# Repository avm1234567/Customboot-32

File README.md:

<h1 align="center">🚀 CustomBoot-32</h1>

<h2 align="center">✨ SRA Eklavya 2025</h2>

## 📑 Table of Contents
* [About the Project](#-about-the-project)  
  - [Aim](#aim)  
  - [Description](#description)  
  - [Tech-Stack](#tech-stack)  
  - [File Structure](#file-structure)  
* [Getting Started](#getting-started)  
  * [Installation](#installation)  
* [Usage](#usage)  
* [Results and Demo](#results-and-demo)  
* [Future Work](#future-work)  
* [Report](#report)
* [Troubleshooting](#troubleshooting)  
* [Contributors](#contributors)  
* [Mentors](#mentors)  
* [Resources](#resources)  
* [Acknowledgements](#acknowledgements)  

---

# ⭐ About the Project

## Aim
Designing a custom PCB with OTA support and a dual-image Bootloader using ESP32 WROOM-32E and STM32F103C8T6.

## Description
The project focuses on creating a custom PCB that integrates the Blue Pill (STM32F103C8T6) with ESP32 WROOM-32E.  
The ESP32 hosts a website, receives two firmwares via OTA, creates memory partitions, and initializes a File System in one of the partitions.  

On the STM side, a dual-image Bootloader requests firmware based on user input, verifies it, allocates it in flash memory, and executes it.  
The firmware transfer is carried out via **UART**.

## Tech-Stack
### Coding Language
<div style="display:flex; align-items:center; margin-bottom:8px;">
  
  <span style="background:#ff6f3c; color:white; padding:4px 10px; border-radius:4px; font-weight:bold;">
    Embedded C
  </span>
</div>

### Libraries
<div style="display:flex; align-items:center; margin-bottom:8px;">
  
  <span style="background:#ff6f3c; color:white; padding:4px 10px; border-radius:4px; font-weight:bold;">
    HAL
  </span>
</div>

<div style="display:flex; align-items:center; margin-bottom:8px;">
  
  <span style="background:#ff6f3c; color:white; padding:4px 10px; border-radius:4px; font-weight:bold;">
    LibOpenCM3
  </span>
</div>

### File Protocol
<div style="display:flex; align-items:center; margin-bottom:8px;">
  
  <span style="background:#ff6f3c; color:white; padding:4px 10px; border-radius:4px; font-weight:bold;">
    SPIFFS
  </span>
</div>

### Communication Protocols
<div style="display:flex; align-items:center; margin-bottom:8px;">
  
  <span style="background:#ff6f3c; color:white; padding:4px 10px; border-radius:4px; font-weight:bold;">
    UART
  </span>
</div>
<div style="display:flex; align-items:center; margin-bottom:8px;">
  
  <span style="background:#ff6f3c; color:white; padding:4px 10px; border-radius:4px; font-weight:bold;">
    OTA
  </span>
</div>
<br><br>

<br><br>

## 📁 File Structure

```
.
├── assets  #All images and test videos
│   ├── 2WayUART.mp4
│   ├── 3D-view back.png
│   ├── 3D-view.png
│   ├── EmbedC.png
│   ├── Final_PCB.png
│   ├── HAL.png
│   ├── LibOpenCM3.png
│   ├── OTA.png
│   ├── PCBSC1.png
│   ├── PCBSC2.png
│   ├── Routing.png
│   ├── SimpleBootloader.mp4
│   ├── SPIFFS.png
│   ├── UART.png
│   ├── website.png
│   ├── Wireless_CMD_Test.mp4
│   └── WorkingVideo.mp4
├── CustomBoot-32  #All the firmwares for both ESP as well as STM
│   ├── 1. OTA
│   ├── 2. Dual_Image_Bootloader
│   ├── 3. ESP_STM_UART1
│   ├── 4. ESP_STM_UART2
│   ├── 5. ESP_TO_STM_FIRMWARE_VIA_UART
│   ├── 6. ESP_STM_FILE_CRC
│   ├── 7. Controling_ESP_GPIO_Wirelessly
│   └── 8. Wireless_Firmware_Selection_ESP_STM(Additional)
├── Documentation  #Detailed documentation of the project
│   └── Final_DOC.pdf
├── Gerber files  #Files made for fabrication of PCB
│   ├── 4 SRA-B_Cu.gbr
│   ├── 4 SRA-B_Mask.gbr
│   ├── 4 SRA-B_Paste.gbr
│   ├── 4 SRA-B_Silkscreen.gbr
│   ├── 4 SRA-drlnew.zip
│   ├── 4 SRA-drl.rpt
│   ├── 4 SRA-Edge_Cuts.gbr
│   ├── 4 SRA-F_Cu.gbr
│   ├── 4 SRA-F_Mask.gbr
│   ├── 4 SRA-F_Paste.gbr
│   ├── 4 SRA-F_Silkscreen.gbr
│   ├── 4 SRA-job.gbrjob
│   ├── 4 SRA-NPTH-drl.gbr
│   ├── 4 SRA-NPTH-drl_map.gbr
│   ├── 4 SRA-PTH-drl.gbr
│   └── 4 SRA-PTH-drl_map.gbr
├── README.md
└── Schematic files  #Schematics of our PCB
    ├── 4 SRA.kicad_pcb
    ├── 4 SRA.kicad_sch
    └── untitled.kicad_sch

```

---

## 🚀 Getting Started

### Installation
1. Clone the repo  
   ```bash
   git clone https://github.com/avm1234567/Customboot-32.git
   ```
2. Navigate to the project directory  
   ```bash
   cd CustomBoot-32
   ```

---

## Usage

The codes used in our project are in the 'CustomBoot-32' directory. 

### 1. OTA

- From the CustomBoot-32 directory head to the OTA directory.
```
cd 1. OTA
```

- In the code enter the SSID and password of your wifi in line 16 and 17.
```
#define WIFI_SSID "Your_SSID"
#define WIFI_PASS "Your_Password"
```

- Then open ESP-IDF Powershell and build the project.
```
idf.py fullclean
idf.py build
```

- After the build is complete flash it.
```
idf.py flash monitor 
```

### 2. Dual_Image_Bootloader

- To generate the bin files open this project in STM32CubeIDE and build it 

- To flash this Code use STM32CubeProgrammer. Change your directory to Dual image bootloader directory. 

- After opening the directory first flash the LED_BLINK_2 bin file into STM-32 at the Start Address '0x08006000'. The path for the bin is: 
```
CustomBoot-32/2. Dual_Image_Bootloader/LED_BLINK_2/Debug/LED_BLINK_2.bin
```

- After flashing the first bin file flash the LED_BLINK bin file into STM-32 at the Start Address '0x08004000'. The path for the bin is:
```
CustomBoot-32/2. Dual_Image_Bootloader/LED_BLINK/Debug/LED_BLINK.bin
```

- Lastly, flash the Bootloader at the Start Address '0x08000000'. The path for the bin is:
```
CustomBoot-32/2. Dual_Image_Bootloader/Learning_Bootloader/Debug/Learning_Bootloader.bin
```

- Press the 'Start Programming' button to run the program.

### 3. ESP_STM_UART1

- To run the ESP side of the code change your directory to 'ESP_STM_COMM'.
```
cd 3. ESP_STM_UART1\ESP_STM_COMM
```

- After that build the code and flash it 
```
idf.py fullclean
idf.py build
idf.py flash monitor 
```

- To flash the STM code, open STM32CubeIDE and generate the build files.

- After generating flash the bin file into the STM using STM32CubeProgrammer at Start Address '0x08000000'

### 4. ESP_STM_UART2

- To run the ESP side of the code change your directory to 'ESP_STM_COMM'.
```
cd 3. ESP_STM_UART2\ESP_STM_COMM
```

- After that build the code and flash it 
```
idf.py fullclean
idf.py build
idf.py flash monitor 
```

- To flash the STM code, open STM32CubeIDE and generate the build files.

- After generating flash the bin file into the STM using STM32CubeProgrammer at Start Address '0x08000000'.

### 5. ESP_TO_STM_FIRMWARE_VIA_UART

-- To run the ESP side of the code change your directory to 'OTA'.
```
cd 5. ESP_TO_STM_FIRMWARE_VIA_UART\OTA
```

- After that build the code and flash it 
```
idf.py build
idf.py flash monitor 
```

- To flash the STM code, open STM32CubeIDE and generate the build files. You will find the bin files in the path
```
CustomBoot-32/5. ESP_TO_STM_FIRMWARE_VIA_UART/Learning_Bootloader/Debug/Learning_Bootloader.bin
```

- After generating flash the bin file into the STM using STM32CubeProgrammer at Start Address '0x08000000'.

### 6. ESP_STM_FILE CRC

- Download libopencm3 by cloning it to run bootloader file
```
git clone https://github.com/libopencm3/libopencm3.git
cd libopencm3
```
- After that flash the ESP32 in the directory
```
idf.py fullclean
CustomBoot-32/6. ESP_STM_FILE_CRC/OTA
idf.py build flash monitor
```

### 7. Controling_ESP_GPIO_Wirelessly
- Firstly fullclean, then build and flash the project.
```
idf.py fullclean
idf.py build
idf.py flash monitor
```

### 8. Wireless_Firmware_Selection
- Download libopencm3 by cloning it to run bootloader file
```
git clone https://github.com/libopencm3/libopencm3.git
cd libopencm3
```
- After that flash the ESP32 in the directory
```
idf.py fullclean
CustomBoot-32/8. Wireless_Firmware_Selection_ESP_STM(Additional)/OTA
idf.py build flash monitor
```

## 📸 Results

**Screenshot of our custom PCB:**  

|            Front            |            Back            |
| --------------------------- | -------------------------- |
|  |  |

## Demo:  
[Working Demo of final PCB](https://drive.google.com/file/d/1Z0VfDI0KjEA28zM6vQ-hMSaG2jekwzWR/view?usp=drive_link)  

For other results and test videos, please check our [Google Drive](https://drive.google.com/drive/folders/1JogM4m4yME66ZIJGMlyX8mcmxp7ndMSk?usp=drive_link).

## Report
Refer our own [report](https://drive.google.com/file/d/13CS2zIfVXfLGR-wP4OjCv9lpuOwN3wu8/view?usp=drive_link) of project where we explain the entire process in detail.

## 🛠 Troubleshooting
* ERC rule check errors in PCB schematics.  
* Routing issues in compact areas while adhering to manufacturer constraints.  
* Wi-Fi SSID and password options not appearing in Menuconfig.  
* CMakeLists errors affecting SPIFFS initialization.  
* Partition table not being detected.  
* SPIFFS initialization failure at runtime.  
* Favicon loading errors.  
* OTA binaries containing unnecessary bloatware.  
* UART initialization issues.  
* Binary file transfer failures.  
* Errors in custom file protocol implementation.  
* End-byte transmission errors during communication.  
* Application jump not functioning correctly (MSP not set).  
* Correct HAL-like application jump with LibOpenCM3.  
* Schematic issues resolved through perfboard prototyping and testing.  

---

## 👥 Contributors
* [Varun Patil](https://github.com/varun05050505)  
* [Omkar Nanajkar](https://github.com/nomkar24)  
* [Archit More](https://github.com/avm1234567)  

## 🎓 Mentors
* [Prithvi Tambewagh](https://github.com/rkt-1597)  
* [Shaunak Datar](https://github.com/ShaunakKDatar)  
* [Vishal Mutha](https://github.com/Vishal-Mutha)  

---

## 📚 Resources

- [Bootloader basics (EmbeTronicx)](https://embetronicx.com/tutorials/microcontrollers/stm32/bootloader/bootloader-basics/)  
- [EmbeddedInventor: Bootloader](https://embeddedinventor.com/embedded-bootloader-and-booting-process-explained/)  
- [Getting Started with STM32](https://youtube.com/playlist?list=PLNyfXcjhOAwO5HNTKpZPsqBhelLF2rWQx)  
- [Bare-metal UART STM32](https://vivonomicon.com/2020/06/28/bare-metal-stm32-programming-part-10-uart-communication/)  
- [ESP32 UART](https://docs.espressif.com/projects/esp-idf/en/stable/esp32/api-reference/peripherals/uart.html)  
- [CRC32 for STM](https://www.st.com/resource/en/application_note/an4187-using-the-stm32-hardware-crc-unit-stmicroelectronics.pdf)  
- [LibOpenCM3 documentation](https://libopencm3.org/docs/latest/stm32f1/html/modules.html)
- [SPIFFS](https://docs.espressif.com/projects/esp-idf/en/stable/esp32/api-reference/storage/spiffs.html)  
- [FreeRTOS](https://my-esp-idf.readthedocs.io/en/latest/api-guides/freertos-smp.html#tasks-and-task-creation)  
- [ESP Web Server Handling](https://esp32tutorials.com/esp32-web-server-esp-idf/)  
- [File Transfer Protocols](https://www.geeksforgeeks.org/computer-networks/xmodem-file-transfer-protocol/)

---

## 🙏 Acknowledgements
We are extremely grateful to our mentors – **Prithvi Tambewagh, Shaunak Datar, and Vishal Mutha** – for their guidance and support throughout the course of this project.  

We also thank [SRA-VJTI](https://sravjti.in/) for their support in organizing [Eklavya 2025](https://sravjti.in/projects/eklavya/) and for providing us the opportunity to work on this project.

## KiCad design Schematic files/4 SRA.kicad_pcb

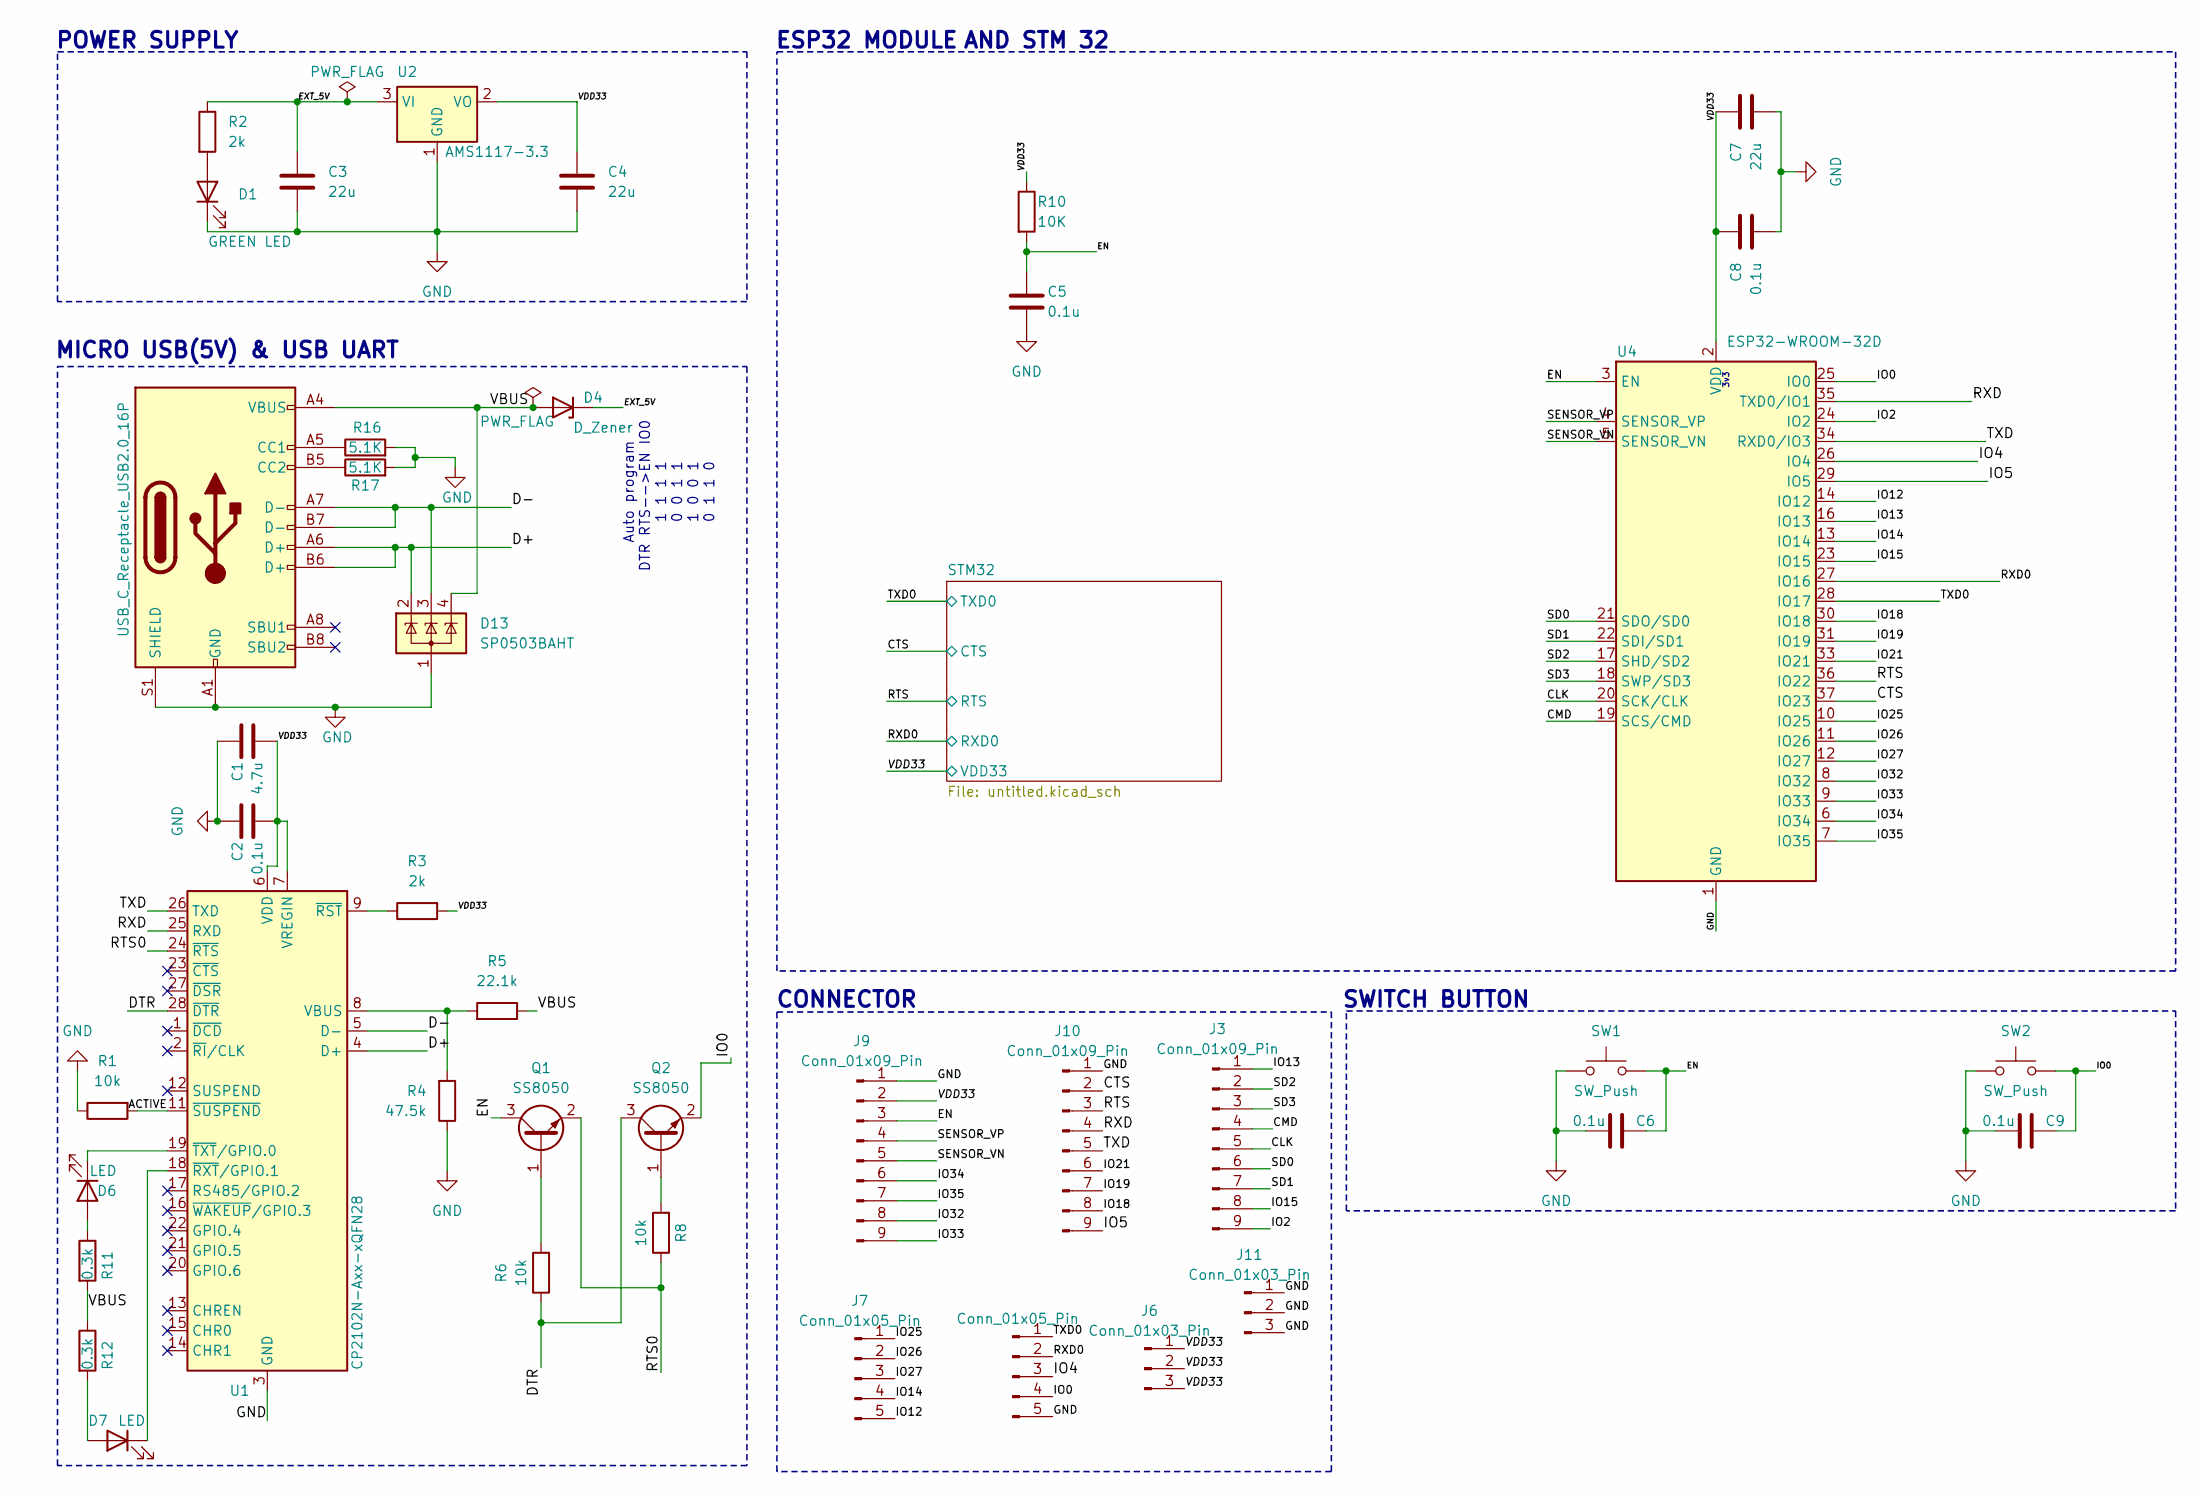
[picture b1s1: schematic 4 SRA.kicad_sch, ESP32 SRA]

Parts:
C1: 4.7u; C_0805_2012Metric_Pad1.18x1.45mm_HandSolder
C2, C5, C6, C8, C9: 0.1u; C_0805_2012Metric_Pad1.18x1.45mm_HandSolder
C3, C4, C7: 22u; C_0805_2012Metric_Pad1.18x1.45mm_HandSolder
D1: GREEN LED; LED_0805_2012Metric_Pad1.15x1.40mm_HandSolder
D4: D_Zener; D_0805_2012Metric_Pad1.15x1.40mm_HandSolder
D6, D7: LED; LED_0805_2012Metric_Pad1.15x1.40mm_HandSolder
D13: SP0503BAHT; SOT-143
J2: USB_C_Receptacle_USB2.0_16P; USB_C_Receptacle_HRO_TYPE-C-31-M-12
J3, J9, J10: Conn_01x09_Pin; PinHeader_1x09_P2.54mm_Vertical
J6, J11: Conn_01x03_Pin; PinHeader_1x03_P2.54mm_Vertical
J7, J8: Conn_01x05_Pin; PinHeader_1x05_P2.54mm_Vertical
Q1, Q2: SS8050; SOT-23
R1, R6, R8: 10k; R_0805_2012Metric_Pad1.20x1.40mm_HandSolder
R2, R3: 2k; R_0805_2012Metric_Pad1.20x1.40mm_HandSolder
R4: 47.5k; R_0805_2012Metric_Pad1.20x1.40mm_HandSolder
R5: 22.1k; R_0805_2012Metric_Pad1.20x1.40mm_HandSolder
R10: 10K; R_0805_2012Metric_Pad1.20x1.40mm_HandSolder
R11, R12: 0.3k; R_0805_2012Metric_Pad1.20x1.40mm_HandSolder
R16, R17: 5.1K; R_0805_2012Metric
SW1, SW2: SW_Push; SW_Push_SPST_NO_Alps_SKRK
U1: CP2102N-Axx-xQFN28; QFN-28-1EP_5x5mm_P0.5mm_EP3.35x3.35mm
U2: AMS1117-3.3; SOT-223-3_TabPin2
U4: ESP32-WROOM-32D

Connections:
/ACTIVE: R1.2, U1.11 (~SUSPEND)
/CLK: J3.5, U4.20 (SCK/CLK)
/CMD: J3.4, U4.19 (SCS/CMD)
/CTS: J10.2, U4.37 (IO23); also elsewhere on the board
/D+: D13.2 (K), J2.A6 (D+), J2.B6 (D+), U1.4 (D+)
/D-: D13.3 (K), J2.A7 (D-), J2.B7 (D-), U1.5 (D-)
/DTR: Q2.3 (C), R6.1, U1.28 (~DTR)
/EN: C5.1, C6.1, J9.3, Q1.3 (C), R10.2, SW1.2, U4.3 (EN)
/EXT_5V: C3.1, D4.1 (K), R2.1, U2.3 (VI)
/IO0: C9.1, J8.4, Q2.2 (E), SW2.2, U4.25 (IO0)
/IO2: J3.9, U4.24 (IO2)
/IO4: J8.3, U4.26 (IO4)
/IO5: J10.9, U4.29 (IO5)
/IO12: J7.5, U4.14 (IO12)
/IO13: J3.1, U4.16 (IO13)
/IO14: J7.4, U4.13 (IO14)
/IO15: J3.8, U4.23 (IO15)
/IO18: J10.8, U4.30 (IO18)
/IO19: J10.7, U4.31 (IO19)
/IO21: J10.6, U4.33 (IO21)
/IO25: J7.1, U4.10 (IO25)
/IO26: J7.2, U4.11 (IO26)
/IO27: J7.3, U4.12 (IO27)
/IO32: J9.8, U4.8 (IO32)
/IO33: J9.9, U4.9 (IO33)
/IO34: J9.6, U4.6 (IO34)
/IO35: J9.7, U4.7 (IO35)
/RTS: J10.3, U4.36 (IO22); also elsewhere on the board
/RTS0: Q1.2 (E), R8.1, U1.24 (~RTS)
/RXD: J10.4, U1.25 (RXD), U4.35 (TXD0/IO1)
/RXD0: J8.2, U4.27 (IO16); also elsewhere on the board
/SD0: J3.6, U4.21 (SDO/SD0)
/SD1: J3.7, U4.22 (SDI/SD1)
/SD2: J3.2, U4.17 (SHD/SD2)
/SD3: J3.3, U4.18 (SWP/SD3)
/SENSOR_VN: J9.5, U4.5 (SENSOR_VN)
/SENSOR_VP: J9.4, U4.4 (SENSOR_VP)
/TXD: J10.5, U1.26 (TXD), U4.34 (RXD0/IO3)
/TXD0: J8.1, U4.28 (IO17); also elsewhere on the board
/VBUS: D4.2 (A), D13.4 (K), J2.A4 (VBUS), J2.A9 (VBUS), J2.B4 (VBUS), J2.B9 (VBUS), R5.1, R11.2, R12.1
GND: C1.1, C2.1, C3.2, C4.2, C5.2, C6.2, C7.2, C8.2, C9.2, D1.1 (K), D13.1 (A), J2.A1 (GND), J2.A12 (GND), J2.B1 (GND), J2.B12 (GND), J2.S1 (SHIELD), J8.5, J9.1, J10.1, J11.1, J11.2, J11.3, R1.1, R4.1, R16.2, R17.2, SW1.1, SW2.1, U1.3 (GND), U1.29 (GND), U2.1 (GND), U4.1 (GND), U4.15 (GND), U4.38 (GND), U4.39 (GND); also elsewhere on the board
unnamed: D1.2 (A), R2.2
unnamed: D6.2 (A), R11.1
unnamed: D6.1 (K), U1.19 (~TXT/GPIO.0)
unnamed: D7.2 (A), R12.2
unnamed: D7.1 (K), U1.18 (~RXT/GPIO.1)
unnamed: J2.A5 (CC1), R16.1
unnamed: J2.B5 (CC2), R17.1
unnamed: Q1.1 (B), R6.2
unnamed: Q2.1 (B), R8.2
unnamed: R4.2, R5.2, U1.8 (VBUS)
unnamed: R3.1, U1.9 (~RST)
VDD33: C1.2, C2.2, C4.1, C7.1, C8.1, J6.1, J6.2, J6.3, J9.2, R3.2, R10.1, U1.6 (VDD), U1.7 (VREGIN), U2.2 (VO), U4.2 (VDD); also elsewhere on the board

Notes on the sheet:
3v3
Auto program DTR RTS-->EN IO0 1 1 1 1 0 0 1 1 1 0 0 1 0 1 1 0
ESP32 MODULE
MICRO USB(5V) & USB UART
CONNECTOR
AND STM 32
POWER SUPPLY
SWITCH BUTTON

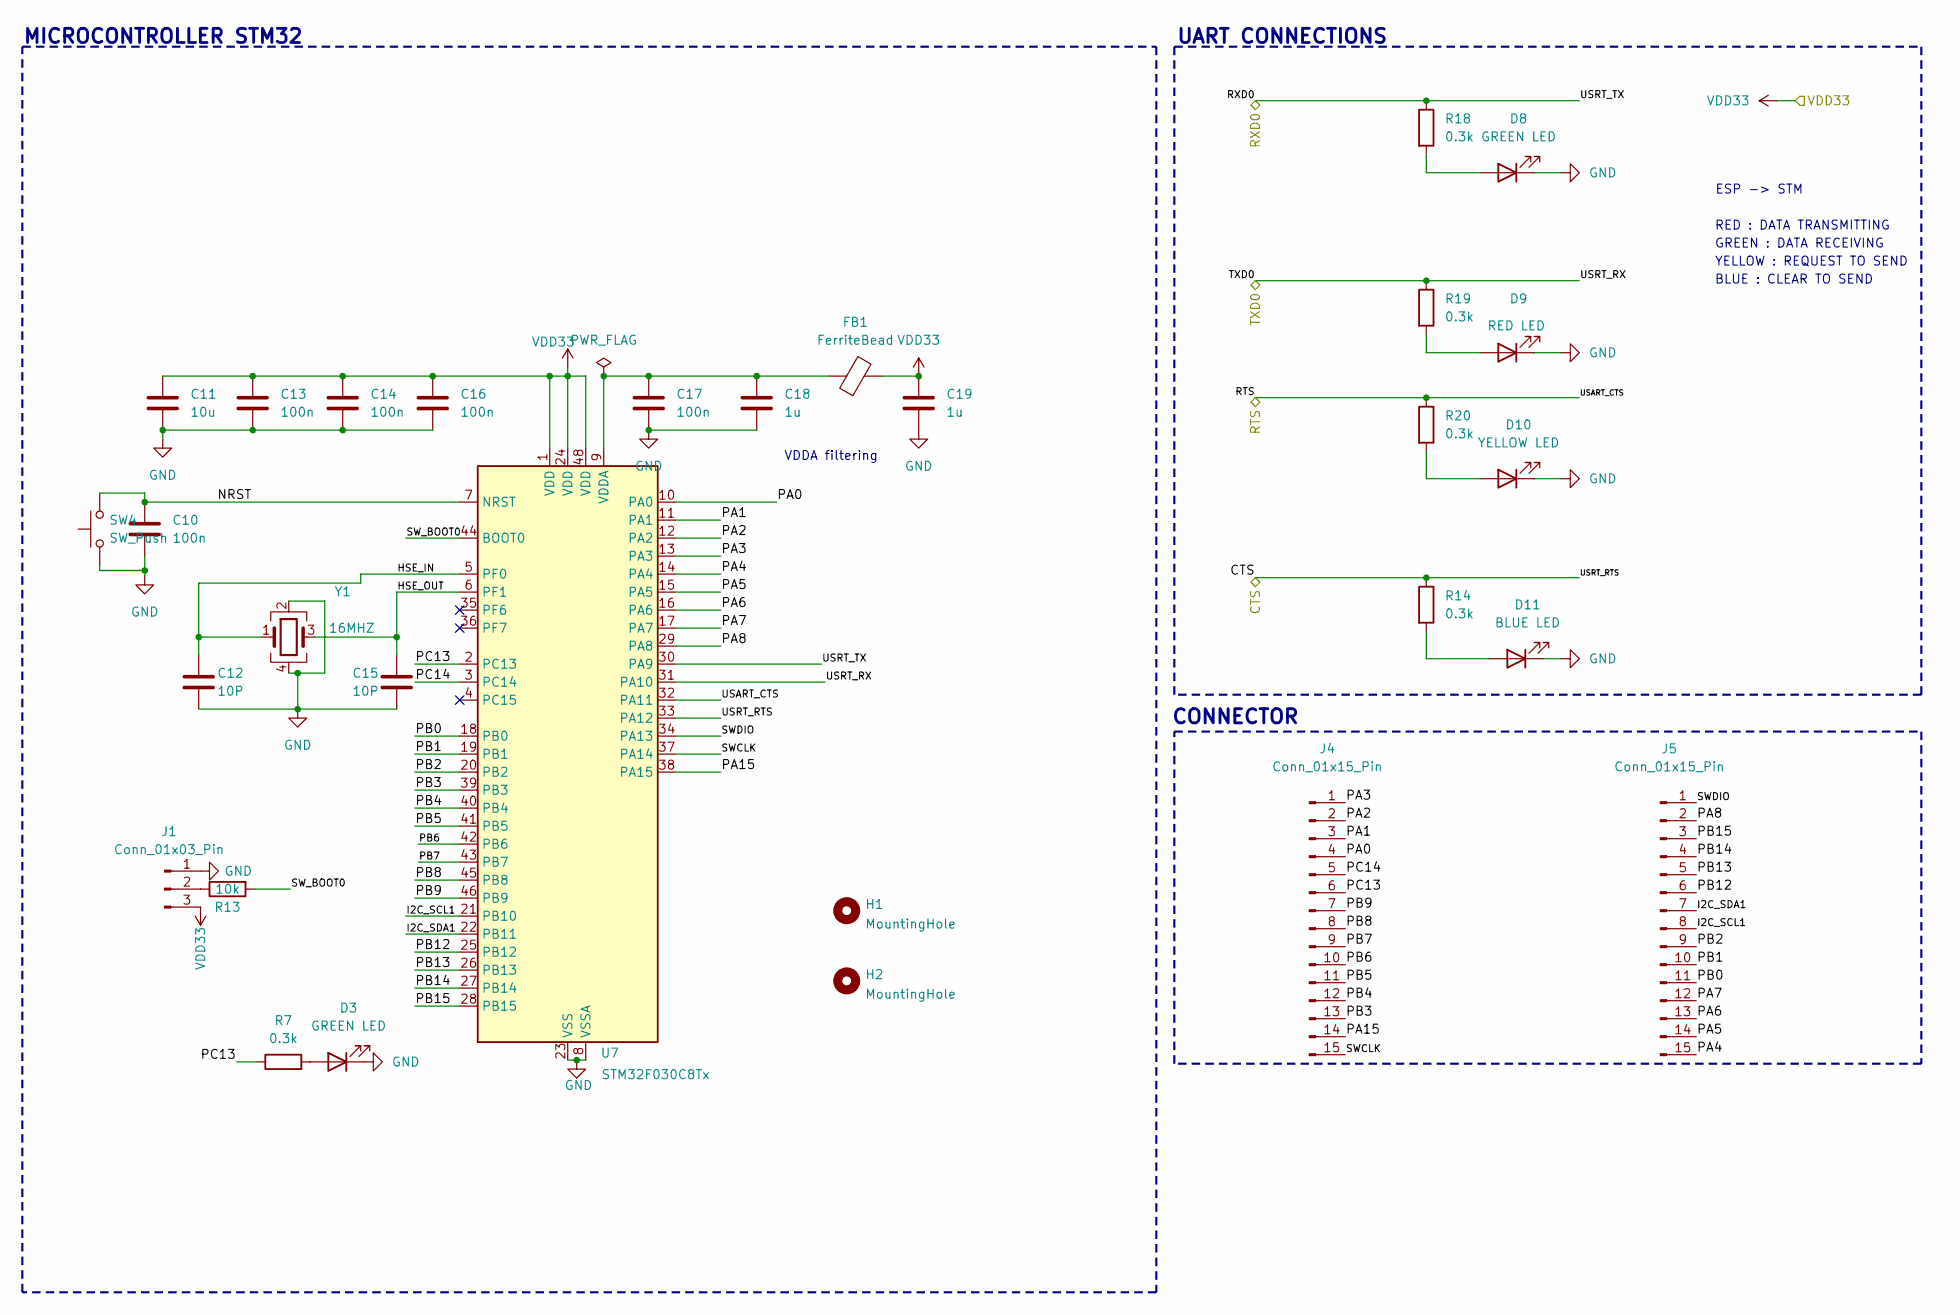
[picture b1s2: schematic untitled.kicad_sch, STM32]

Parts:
C10, C13, C14, C16, C17: 100n; C_0805_2012Metric_Pad1.18x1.45mm_HandSolder
C11: 10u; C_0805_2012Metric_Pad1.18x1.45mm_HandSolder
C12, C15: 10P; C_0805_2012Metric_Pad1.18x1.45mm_HandSolder
C18, C19: 1u; C_0805_2012Metric_Pad1.18x1.45mm_HandSolder
D3, D8: GREEN LED; LED_0805_2012Metric_Pad1.15x1.40mm_HandSolder
D9: RED LED; LED_0805_2012Metric_Pad1.15x1.40mm_HandSolder
D10: YELLOW LED; LED_0805_2012Metric_Pad1.15x1.40mm_HandSolder
D11: BLUE LED; LED_0805_2012Metric_Pad1.15x1.40mm_HandSolder
FB1: FerriteBead; L_0805_2012Metric_Pad1.05x1.20mm_HandSolder
H1, H2: MountingHole; MountingHole_3.2mm_M3
J1: Conn_01x03_Pin; PinHeader_1x03_P2.54mm_Vertical
J4, J5: Conn_01x15_Pin; PinHeader_1x15_P2.54mm_Vertical
R7, R14, R18, R19, R20: 0.3k; R_0805_2012Metric_Pad1.20x1.40mm_HandSolder
R13: 10k; R_0805_2012Metric_Pad1.20x1.40mm_HandSolder
SW4: SW_Push; SW_Push_SPST_NO_Alps_SKRK
U7: STM32F030C8Tx; LQFP-48_7x7mm_P0.5mm
Y1: 16MHZ; Crystal_SMD_2016-4Pin_2.0x1.6mm

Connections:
/CTS: R14.1, U7.33 (PA12); also elsewhere on the board
/RTS: R20.1, U7.32 (PA11); also elsewhere on the board
/RXD0: R18.1, U7.30 (PA9); also elsewhere on the board
/STM32/HSE_IN: C12.1, U7.5 (PF0), Y1.1
/STM32/HSE_OUT: C15.1, U7.6 (PF1), Y1.3
/STM32/I2C_SCL1: J5.8, U7.21 (PB10)
/STM32/I2C_SDA1: J5.7, U7.22 (PB11)
/STM32/NRST: C10.1, SW4.2, U7.7 (NRST)
/STM32/PA0: J4.4, U7.10 (PA0)
/STM32/PA1: J4.3, U7.11 (PA1)
/STM32/PA2: J4.2, U7.12 (PA2)
/STM32/PA3: J4.1, U7.13 (PA3)
/STM32/PA4: J5.15, U7.14 (PA4)
/STM32/PA5: J5.14, U7.15 (PA5)
/STM32/PA6: J5.13, U7.16 (PA6)
/STM32/PA7: J5.12, U7.17 (PA7)
/STM32/PA8: J5.2, U7.29 (PA8)
/STM32/PA15: J4.14, U7.38 (PA15)
/STM32/PB0: J5.11, U7.18 (PB0)
/STM32/PB1: J5.10, U7.19 (PB1)
/STM32/PB2: J5.9, U7.20 (PB2)
/STM32/PB3: J4.13, U7.39 (PB3)
/STM32/PB4: J4.12, U7.40 (PB4)
/STM32/PB5: J4.11, U7.41 (PB5)
/STM32/PB6: J4.10, U7.42 (PB6)
/STM32/PB7: J4.9, U7.43 (PB7)
/STM32/PB8: J4.8, U7.45 (PB8)
/STM32/PB9: J4.7, U7.46 (PB9)
/STM32/PB12: J5.6, U7.25 (PB12)
/STM32/PB13: J5.5, U7.26 (PB13)
/STM32/PB14: J5.4, U7.27 (PB14)
/STM32/PB15: J5.3, U7.28 (PB15)
/STM32/PC13: J4.6, R7.1, U7.2 (PC13)
/STM32/PC14: J4.5, U7.3 (PC14)
/STM32/SWCLK: J4.15, U7.37 (PA14)
/STM32/SWDIO: J5.1, U7.34 (PA13)
/STM32/SW_BOOT0: R13.2, U7.44 (BOOT0)
/TXD0: R19.1, U7.31 (PA10); also elsewhere on the board
GND: C10.2, C11.2, C12.2, C13.2, C14.2, C15.2, C16.2, C17.2, C18.2, C19.2, D3.1 (K), D8.1 (K), D9.1 (K), D10.1 (K), D11.1 (K), J1.1, SW4.1, U7.8 (VSSA), U7.23 (VSS), U7.47 (VSS), Y1.2, Y1.4; also elsewhere on the board
unnamed: D3.2 (A), R7.2
unnamed: D8.2 (A), R18.2
unnamed: D9.2 (A), R19.2
unnamed: D10.2 (A), R20.2
unnamed: D11.2 (A), R14.2
unnamed: J1.2, R13.1
unnamed: C17.1, C18.1, FB1.1, U7.9 (VDDA)
VDD33: C11.1, C13.1, C14.1, C16.1, C19.1, FB1.2, J1.3, U7.1 (VDD), U7.24 (VDD), U7.48 (VDD); also elsewhere on the board

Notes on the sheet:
GREEN : DATA RECEIVING
RED : DATA TRANSMITTING
YELLOW : REQUEST TO SEND
ESP -> STM
CONNECTOR
MICROCONTROLLER STM32
VDDA filtering
UART CONNECTIONS
BLUE : CLEAR TO SEND

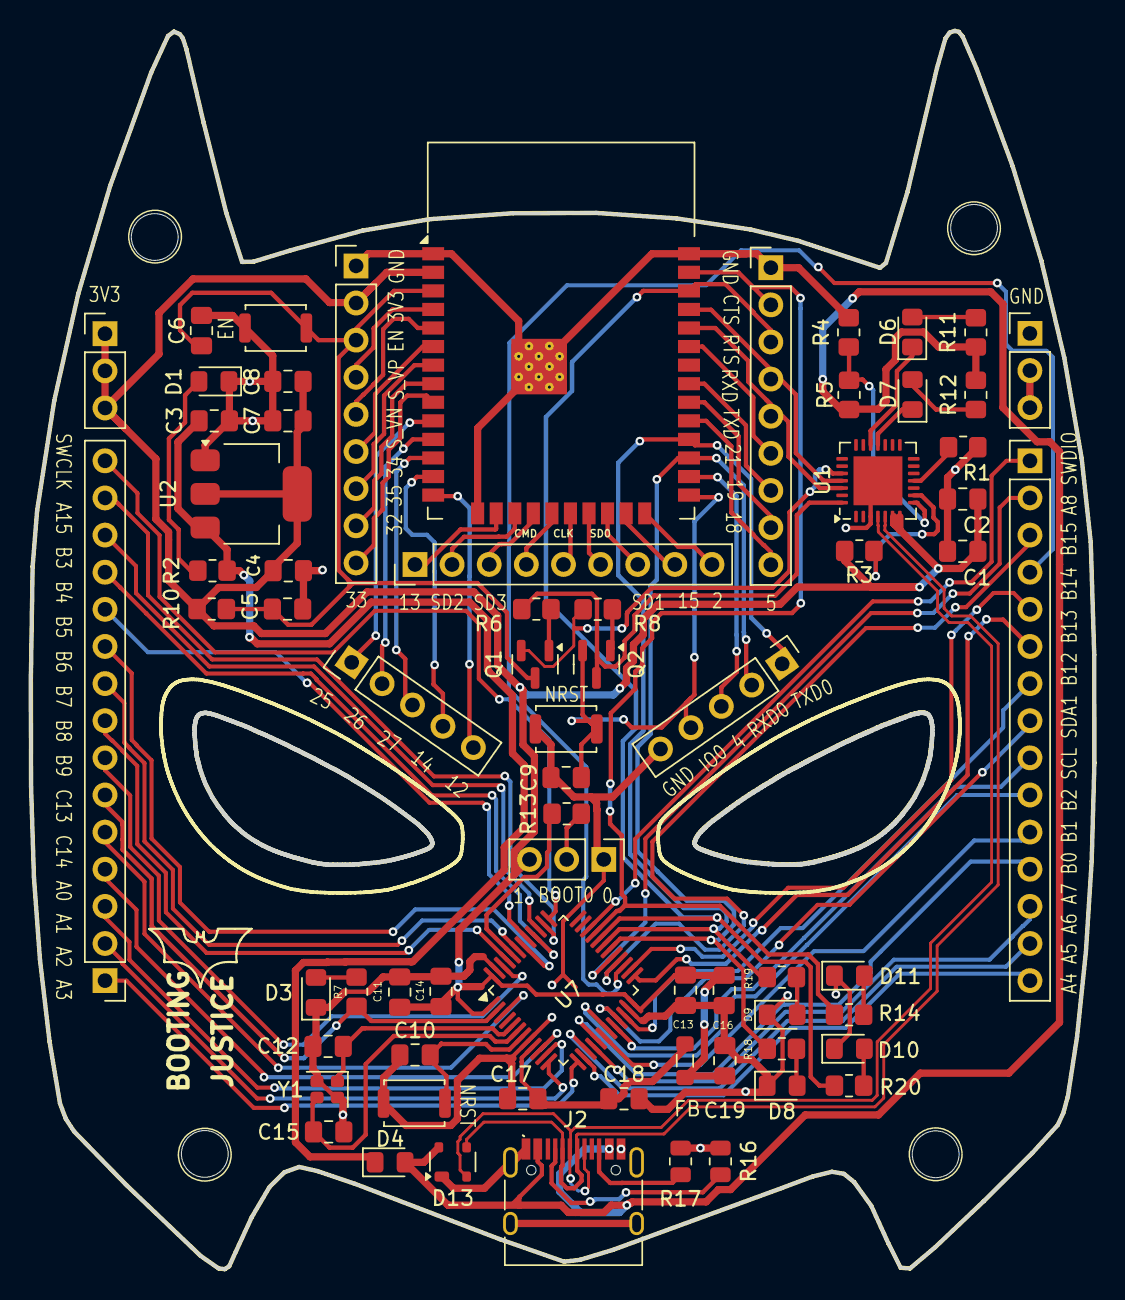
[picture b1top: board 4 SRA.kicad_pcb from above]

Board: 2 copper layers, 72.8 x 84.7 mm, 73 parts (0 on the bottom side), 94 nets.

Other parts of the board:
H2#2, H2#3: MountingHole; MountingHole_3.2mm_M3

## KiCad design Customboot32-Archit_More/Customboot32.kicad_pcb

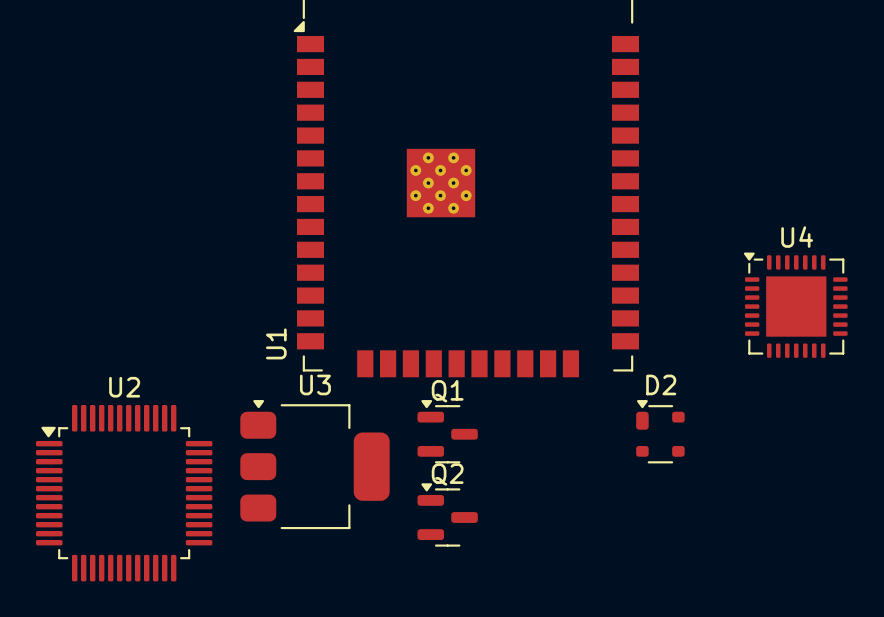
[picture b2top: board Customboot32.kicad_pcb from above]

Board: 2 copper layers, 7 parts (0 on the bottom side), 13 nets, no tracks yet.

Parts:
D2: SP0503BAHT; SOT-143
Q1, Q2: SS8050; SOT-23
U1: ESP32-WROOM-32D
U2: STM32F103C8T6; LQFP-48_7x7mm_P0.5mm
U3: AMS1117-3.3; SOT-223-3_TabPin2
U4: CP2102N-Axx-xQFN28; QFN-28-1EP_5x5mm_P0.5mm_EP3.35x3.35mm

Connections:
+3.3V: U1.2 (VDD), U2.1 (VBAT), U2.24 (VDD), U2.36 (VDD), U2.48 (VDD), U3.2 (VO), U4.6 (VDD), U4.7 (VREGIN)
/TXD2: U1.28 (IO17), U2.31 (PA10)
CTS0: U1.31 (IO19), U2.33 (PA12)
DTR: Q1.2 (E), U4.28 (~DTR)
EN: Q2.3 (C), U1.3 (EN)
GND: D2.1 (A), U1.1 (GND), U1.15 (GND), U1.38 (GND), U1.39 (GND), U2.8 (VSSA), U2.23 (VSS), U2.35 (VSS), U2.47 (VSS), U3.1 (GND), U4.3 (GND), U4.29 (GND)
IO0: Q1.3 (C), U1.25 (IO0)
unnamed: D2.3 (K), U4.4 (D+)
unnamed: D2.4 (K), U4.5 (D-)
RTS: Q2.2 (E), U4.24 (~RTS)
RXD0: U1.34 (RXD0/IO3), U4.26 (TXD)
TXDO: U1.35 (TXD0/IO1), U4.25 (RXD)
VBUS: D2.2 (K), U3.3 (VI)

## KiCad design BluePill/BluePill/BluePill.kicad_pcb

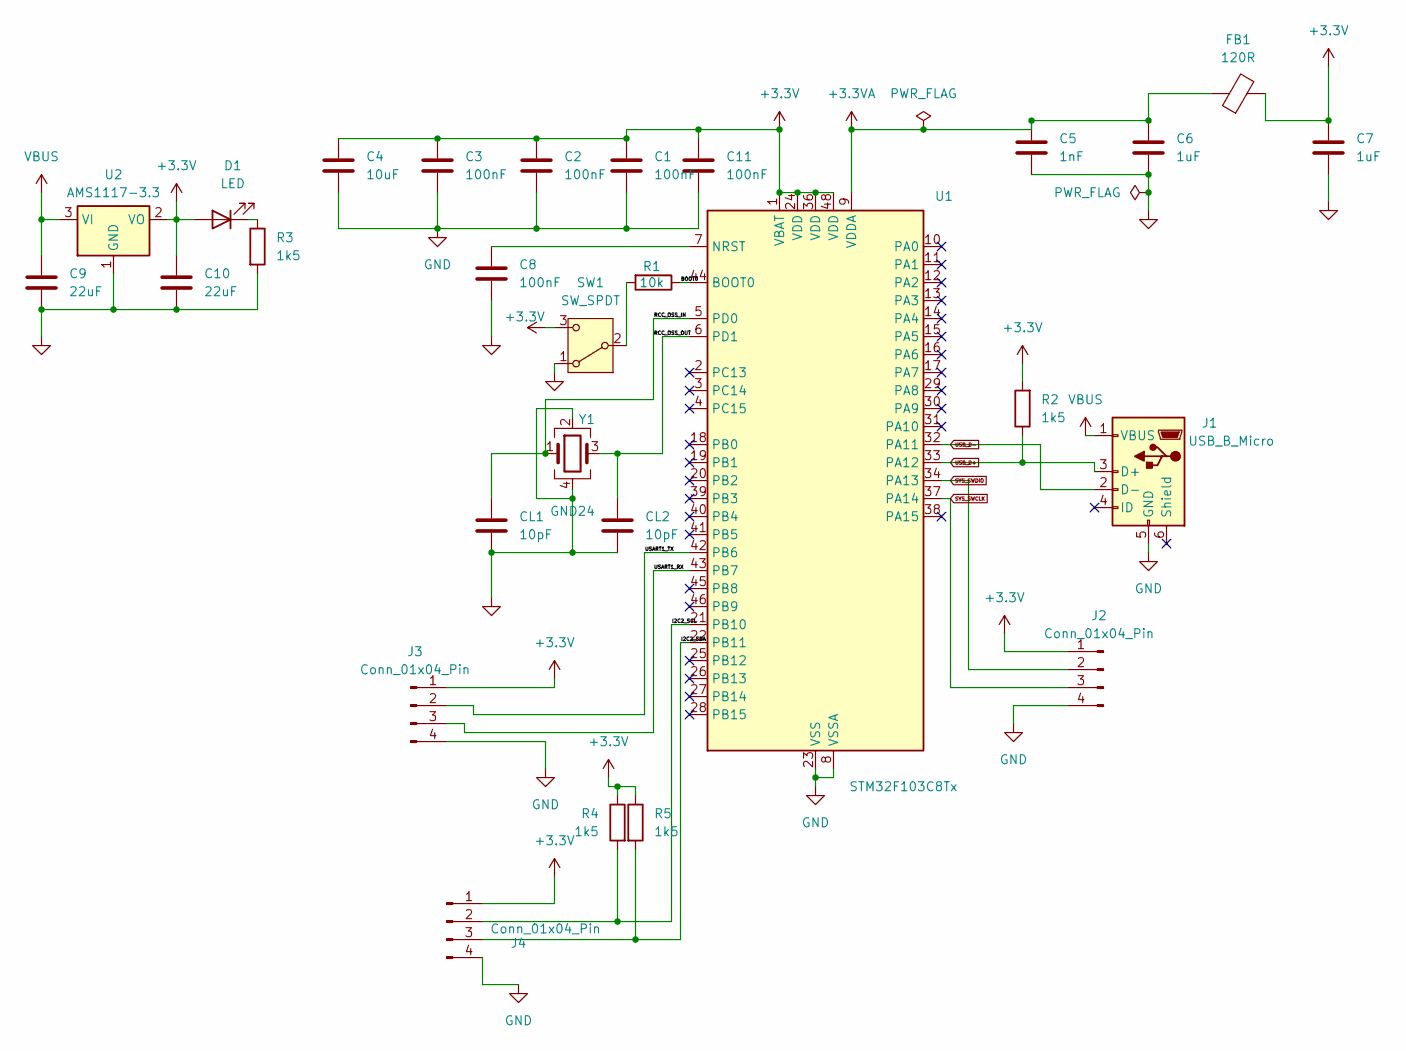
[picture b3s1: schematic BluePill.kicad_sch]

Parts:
C1, C2, C3, C8, C11: 100nF; C_0402_1005Metric
C4: 10uF; C_0402_1005Metric
C5: 1nF; C_0402_1005Metric
C6, C7: 1uF; C_0402_1005Metric
C9, C10: 22uF; C_0402_1005Metric
CL1, CL2: 10pF; C_0402_1005Metric
D1: LED; LED_0603_1608Metric
FB1: 120R; L_0603_1608Metric
J1: USB_B_Micro; USB_Micro-B_Wuerth_629105150521
J2, J3, J4: Conn_01x04_Pin; PinHeader_1x04_P2.54mm_Vertical
R1: 10k; R_0402_1005Metric
R2, R3, R4, R5: 1k5; R_0402_1005Metric
SW1: SW_SPDT; SW_SPDT_PCM12
U1: STM32F103C8Tx; LQFP-48_7x7mm_P0.5mm
U2: AMS1117-3.3; SOT-223-3_TabPin2
Y1: GND24; Crystal_SMD_3225-4Pin_3.2x2.5mm

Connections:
+3.3V: C1.1, C2.1, C3.1, C4.1, C7.1, C10.1, C11.1, D1.2 (A), FB1.2, J2.1, J3.1, J4.1, R2.2, R4.1, R5.1, SW1.3 (C), U1.1 (VBAT), U1.24 (VDD), U1.36 (VDD), U1.48 (VDD), U2.2 (VO)
+3.3VA: C5.1, C6.1, FB1.1, U1.9 (VDDA)
/BOOT0: R1.1, U1.44 (BOOT0)
/I2C2_SCL: J4.2, R4.2, U1.21 (PB10)
/I2C2_SDA: J4.3, R5.2, U1.22 (PB11)
/RCC_OSS_IN: CL1.1, U1.5 (PD0), Y1.1
/USART1_RX: J3.3, U1.43 (PB7)
/USART1_TX: J3.2, U1.42 (PB6)
<NO NET>: C5.2, C6.2, C7.2, C8.2, C9.2, C10.2, CL1.2, CL2.2, R3.2, SW1.1 (A), U2.1 (GND), Y1.2, Y1.4
GND: C1.2, C2.2, C3.2, C4.2, C11.2, J1.5 (GND), J2.4, J3.4, J4.4, U1.8 (VSSA), U1.23 (VSS), U1.35 (VSS), U1.47 (VSS)
unnamed: D1.1 (K), R3.1
unnamed: R1.2, SW1.2 (B)
unnamed: C8.1, U1.7 (NRST)
unnamed: CL2.1, U1.6 (PD1), Y1.3
SYS_SWCLK: J2.3, U1.37 (PA14)
SYS_SWDIO: J2.2, U1.34 (PA13)
USB_D+: J1.3 (D+), R2.1, U1.33 (PA12)
USB_D-: J1.2 (D-), U1.32 (PA11)
VBUS: C9.1, J1.1 (VBUS), U2.3 (VI)

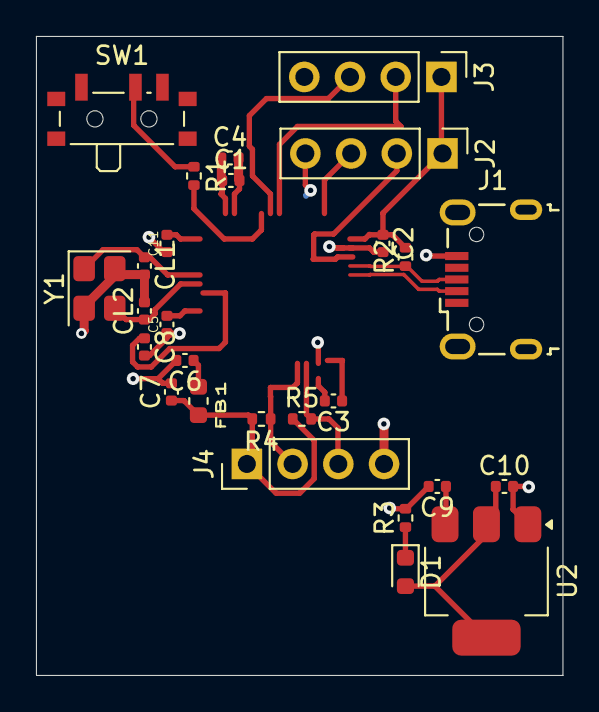
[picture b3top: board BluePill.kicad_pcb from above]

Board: 2 copper layers, 29.2 x 35.5 mm, 27 parts (0 on the bottom side), 12 nets.

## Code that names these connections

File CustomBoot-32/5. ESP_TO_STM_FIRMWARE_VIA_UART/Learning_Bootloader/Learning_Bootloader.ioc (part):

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Mcu.Name=STM32F103C(4-6)Tx
Mcu.Package=LQFP48
Mcu.UserName=STM32F103C6Tx
PA0-WKUP.Signal=GPIO_Input
PA10.Mode=Asynchronous
PA10.Signal=USART1_RX
PA11.Mode=CTS_RTS
PA11.Signal=USART1_CTS
PA12.Mode=CTS_RTS
PA12.Signal=USART1_RTS
PA9.Mode=Asynchronous
PA9.Signal=USART1_TX
PC13-TAMPER-RTC.Signal=GPIO_Output
PD0-OSC_IN.Mode=HSE-External-Oscillator
PD0-OSC_IN.Signal=RCC_OSC_IN
PD1-OSC_OUT.Mode=HSE-External-Oscillator
PD1-OSC_OUT.Signal=RCC_OSC_OUT
RCC.SYSCLKFreq_VALUE=16000000
RCC.SYSCLKSource=RCC_SYSCLKSOURCE_PLLCLK
board=custom

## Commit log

2025-06-26 Readme modified
2025-07-01 Schematic added
2025-07-03 done
2025-07-03 Schematic added -Archit
2025-07-04 Updated Schematics
2025-07-17 Upadted bootloader
2025-07-23 Modified OTA
2025-07-23 ESP OTA code added
2025-07-25 issues solved!!
    Streamlined the design by resolving CP2102N and ESP32 TX/RX pin issues. All necessary footprints were assigned, favoring 0805 SMD components for a compact board layout
2025-07-25 STM32F103C8t6 is changed to STM32F103C6tx
2025-07-25 ADDED NEW TEST
2025-07-29 Dual Image Bootloader
2025-07-29 UART ECHO modified
2025-07-29 OTA+UART added
2025-07-29 Added
2025-07-29 STM Bootloader Added
2025-07-29 UART Test for STM alone using PUTTY
2025-07-29 ESP to STM one way Communication
2025-07-31 Updated repo
2025-07-31 Minor changes
2025-08-02 UPDATED TESTS N README
2025-08-02 Deleted files
2025-08-03 ADDED NEW FILES
2025-08-04 ESP TO STM UART CODE ADDED
2025-08-07 Add ESP_STM_FILE as regular folder
2025-08-07 Varun's work
2025-08-07 LibOpenCM3 code
2025-08-11 ESP to STM bin file transfer via uart using Bare-Metal LibOpenCM3 bootloader
2025-08-12 Battery System Integration Complete
    Added comprehensive battery functionality to the development board, including integrated battery protection circuitry and USB-C charging capability. All schematics have been updated to reflect the ne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
2025-08-12 CRC logic updated
2025-08-12 README.md
2025-08-13 CRC hardware implementation
2025-08-13 minor Fixes
2025-08-16 Reduced bootloader size(LibOpenCM3)
2025-08-19 STM ESP code, non functional
2025-08-19 Modified README
2025-08-23 main modified
2025-08-23 Major restructuring of repo
2025-08-23 README
2025-09-06 README changed
2025-09-06 Documentation
2025-11-24 Updayed build
2026-01-05 Fix mentor GitHub links in README
    Updated mentor links in the README file.
